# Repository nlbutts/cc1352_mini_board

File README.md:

# cc1352_mini_board
This is a small dev board based on the TI CC1352P SOC. It is intended as a small Thread development platform.

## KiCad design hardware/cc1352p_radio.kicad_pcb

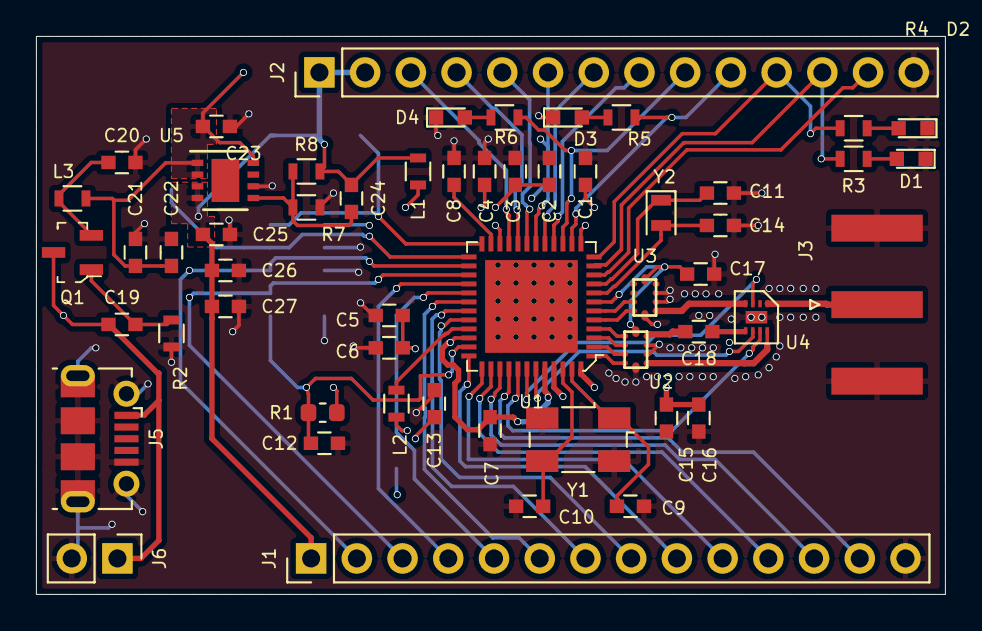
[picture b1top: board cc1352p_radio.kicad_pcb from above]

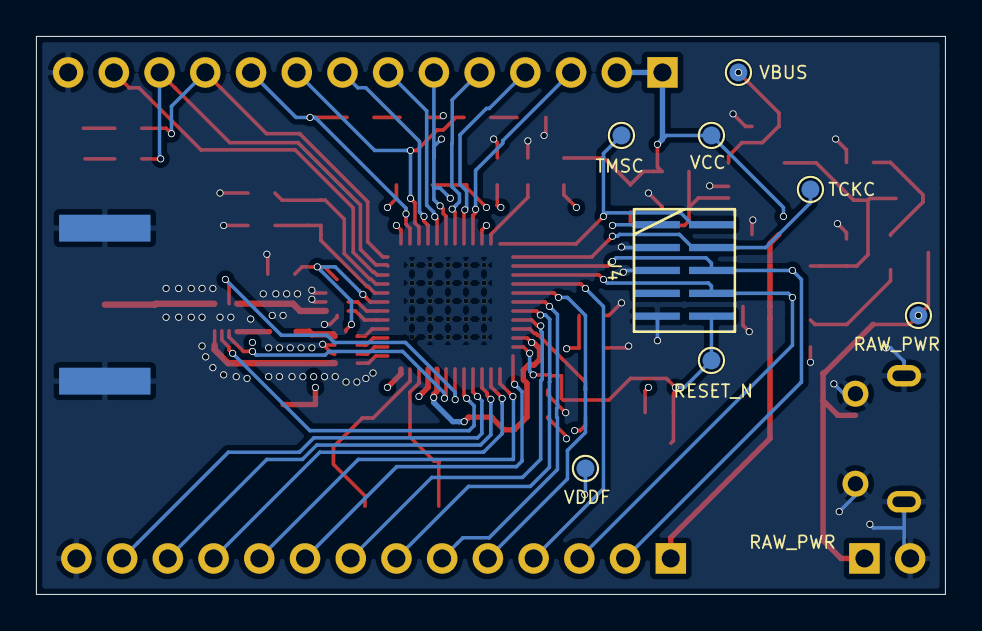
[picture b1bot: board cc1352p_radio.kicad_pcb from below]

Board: 4 copper layers, 50.5 x 31.0 mm, 63 parts (8 on the bottom side), 60 nets.

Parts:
C1, C3, C11: 12p; C_0603
C2, C4, C5, C7, C8, C12, C15, C16, C19, C21, C26: 0.1u; C_0603
C6, C13: 22u; C_0603
C9, C10: DNP; C_0603
C14, C24: 15p; C_0603
C17, C18: 100p; C_0603
C20, C27: 10n; C_0603
C22: 3.3u; C_0603
C23, C25: 2.2u; C_0603
D1, D2, D3, D4: LED; LED_0603
J1, J2: Conn_01x14_Female; PinHeader_1x14_P2.54mm_Vertical
J3: Conn_Coaxial; SMA_Amphenol_132289_EdgeMount
J4: Conn_02x05_Odd_Even; FTSH-105-01-L-DV-K
J5: USB_B_Micro; USB_Micro-B_Molex-105017-0001
J6: Conn_01x02_Male; Pin_Header_Straight_1x02_Pitch2.54mm
L1, L3: BLM18HE152SN1; L_0603
L2: 6.8u; L_0603
Q1: DMG2305UX-13; SOT-23-3
R1: 100k; R_0603_1608Metric
R2: 510k; R_0603
R3, R4, R5, R6: 220; R_0603
R7: 51k; R_0603
R8: 30k; R_0603
TP1, TP2, TP3, TP4, TP5, TP6, TP7: TestPoint; TestPoint_Pad_D1.0mm
U1: CC1352PF3RGZ; QFN-48-1EP_7x7mm
U2, U3: 0900PC15A0036; Johanson_0900PC15A0036
U4: SKY13317-373; MLP-8
U5: TPS79601DR; DFN-8-1EP_3x3mm_Pitch0.65mm
Y1: 48MHz; Crystal_SMD_Abracon_ABM3B-4Pin_5.0x3.2mm
Y2: 32.768kHz; Crystal_SMD_2012-2Pin_2.0x1.2mm

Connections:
/DCDC_SW: L2.1, U1.33
/DIO6: J2.12, R3.1, U1.11
/DIO7: J2.11, R4.1, U1.12
/DIO8: J2.10, R5.1, U1.14
/DIO9: J2.9, R6.1, U1.15
/DIO16: J1.2, J4.6, U1.26
/DIO17: J1.3, J4.8, U1.27
/RESET_N: C12.1, J4.10, R1.2, TP5.1, U1.35
/RF_SEL1: U1.42, U4.3
/RF_SEL2: U1.43, U4.6
/RF_SEL3: U1.41, U4.7
/RX_TX: C17.1, U1.7, U2.5, U3.5
/TCKC: J4.4, TP4.1, U1.25
/TMSC: J4.2, TP3.1, U1.24
GND: C1.2, C2.2, C3.2, C4.2, C5.2, C6.2, C7.2, C8.2, C9.2, C10.2, C11.2, C12.2, C13.2, C14.2, C15.2, C16.2, C17.2, C20.2, C21.2, C22.2, C23.2, C25.2, C26.2, C27.2, D1.1, D2.1, D3.1, D4.1, J1.14, J2.14, J3.2, J4.3, J4.5, J4.9, J5.5, J5.6, J6.2, R2.2, R8.2, U1.49, U2.2, U2.3, U2.10, U3.2, U3.3, U3.10, U4.9, U5.6, Y1.2, Y1.4
unnamed: C8.1, U1.23
unnamed: C9.1, U1.47, Y1.1
unnamed: C10.1, U1.46, Y1.3
unnamed: C11.1, U1.9, Y2.1
unnamed: C14.1, U1.8, Y2.2
unnamed: C18.1, U4.5
unnamed: C18.2, U2.4
unnamed: C19.1, J5.1, J6.1, Q1.3, TP1.1
unnamed: C19.2, Q1.1, R2.1
unnamed: C20.1, L3.1, Q1.2
unnamed: C24.2, R7.2, R8.1, U5.5
unnamed: D1.2, R3.2
unnamed: D2.2, R4.2
unnamed: D3.2, R5.2
unnamed: D4.2, R6.2
unnamed: J1.4, U1.28
unnamed: J1.5, U1.29
unnamed: J1.6, U1.30
unnamed: J1.7, U1.31
unnamed: J1.8, U1.32
unnamed: J1.9, U1.36
unnamed: J1.10, U1.37
unnamed: J1.11, U1.38
unnamed: J1.12, U1.39
unnamed: J1.13, U1.40
unnamed: J2.3, U1.21
unnamed: J2.4, U1.20
unnamed: J2.5, U1.19
unnamed: J2.6, U1.18
unnamed: J2.7, U1.17
unnamed: J2.8, U1.16
unnamed: J2.13, U1.10
unnamed: J3.1, U4.1
unnamed: U1.1, U2.9
unnamed: U1.2, U2.8
unnamed: U1.3, U2.7
unnamed: U1.4, U2.6
unnamed: U1.5, U3.9
unnamed: U1.6, U3.8
unnamed: U2.1, U4.8
unnamed: U3.1, U4.4
VBUS: C21.1, C22.1, C23.1, L3.2, TP2.1, U5.1, U5.2, U5.8
VCC: C24.1, C25.1, C26.1, C27.1, J1.1, J2.1, J2.2, L1.1, R7.1, TP6.1, U5.3, U5.4
VDD: C1.1, C2.1, C3.1, C4.1, C5.1, C6.1, C7.1, J4.1, L1.2, R1.1, U1.13, U1.22, U1.34, U1.44
VDDF: C13.1, C15.1, C16.1, L2.2, TP7.1, U1.45, U1.48

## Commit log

2019-04-12 Initial checkin.
2019-04-12 Routed the board out. Might work.
2019-05-13 Added the software folder.
2019-06-10 Updated to use the new LCD and a newer version of CCS.
